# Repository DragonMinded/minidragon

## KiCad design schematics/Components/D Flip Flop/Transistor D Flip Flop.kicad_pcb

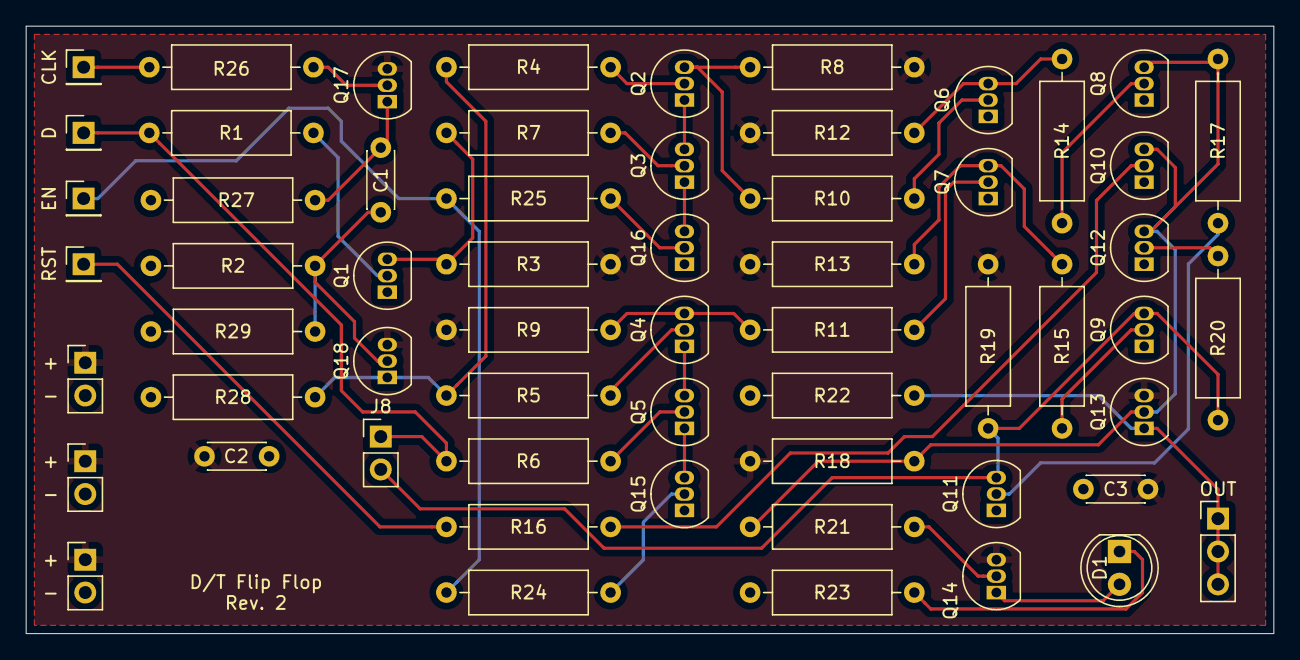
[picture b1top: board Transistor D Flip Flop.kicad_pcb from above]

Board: 2 copper layers, 96.5 x 47.0 mm, 60 parts (0 on the bottom side), 39 nets.

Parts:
C1, C2, C3: 0.1uF; C_Disc_D4.3mm_W1.9mm_P5.00mm
D1: LED; LED_D5.0mm
J1: CLK; PinHeader_1x01_P2.54mm_Vertical
J2: D; PinHeader_1x01_P2.54mm_Vertical
J3: RST; PinHeader_1x01_P2.54mm_Vertical
J4, J5, J6: Power; PinHeader_1x02_P2.54mm_Vertical
J7: OUT; PinHeader_1x03_P2.54mm_Vertical
J8: T-Select; PinHeader_1x02_P2.54mm_Vertical
J9: EN; PinHeader_1x01_P2.54mm_Vertical
Q1, Q2, Q3, Q4, Q5, Q6, Q7, Q8, Q9, Q10, Q11, Q12, Q13, Q14, Q15, Q16, Q17, Q18: 2N2222; TO-92_Inline
R1, R4, R5, R6, R7, R10, R11, R14, R15, R16, R17, R20, R21, R24, R25: 10K; R_Axial_DIN0309_L9.0mm_D3.2mm_P12.70mm_Horizontal
R2, R27, R29: 100; R_Axial_DIN0309_L9.0mm_D3.2mm_P12.70mm_Horizontal
R3, R8, R9, R12, R13, R18, R19, R22, R23, R26, R28: 1K; R_Axial_DIN0309_L9.0mm_D3.2mm_P12.70mm_Horizontal

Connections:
GND: C2.1, C3.1, J4.2, J5.2, J6.2, Q1.1 (E), Q6.1 (E), Q7.1 (E), Q8.1 (E), Q9.1 (E), Q10.1 (E), Q11.1 (E), Q12.1 (E), Q15.1 (E), Q16.1 (E), R2.2, R22.1, R23.1, R27.2, R28.2, R29.2
unnamed: D1.2 (A), Q14.1 (E)
unnamed: D1.1 (K), R23.2
unnamed: J1.1, R26.2
unnamed: J2.1, J8.1, R1.2, R6.2
unnamed: J3.1, R16.2
unnamed: J7.1, J7.2, J7.3, Q13.1 (E), R22.2
unnamed: J8.2, Q9.3 (C), Q11.3 (C), R19.2, R20.2
unnamed: J9.1, R24.2, R25.2
unnamed: Q1.2 (B), R1.1
unnamed: Q1.3 (C), R3.2, R7.2
unnamed: Q2.2 (B), R4.1
unnamed: Q2.3 (C), R8.2, R10.2
unnamed: Q2.1 (E), Q3.3 (C)
unnamed: Q3.2 (B), R7.1
unnamed: Q4.2 (B), R5.1
unnamed: Q4.3 (C), R9.2, R11.2
unnamed: Q4.1 (E), Q5.3 (C)
unnamed: Q5.2 (B), R6.1
unnamed: Q6.2 (B), R10.1
unnamed: Q6.3 (C), R12.2, R14.2
unnamed: Q7.2 (B), R11.1
unnamed: Q7.3 (C), R13.2, R15.2
unnamed: Q8.2 (B), R14.1
unnamed: Q9.2 (B), R15.1
unnamed: Q10.2 (B), R16.1
unnamed: Q8.3 (C), Q10.3 (C), Q12.3 (C), Q13.2 (B), R17.1, R18.1, R21.2
unnamed: Q11.2 (B), R17.2
unnamed: Q12.2 (B), R20.1
unnamed: Q14.2 (B), R21.1
unnamed: Q15.2 (B), R24.1
unnamed: Q5.1 (E), Q15.3 (C)
unnamed: Q16.2 (B), R25.1
unnamed: Q3.1 (E), Q16.3 (C)
unnamed: Q17.2 (B), R26.1
unnamed: C1.1, Q17.1 (E), R27.1
unnamed: C1.2, Q18.2 (B), R2.1, R29.1
unnamed: Q18.1 (E), R4.2, R5.2, R28.1
VCC: C2.2, C3.2, J4.1, J5.1, J6.1, Q13.3 (C), Q14.3 (C), Q17.3 (C), Q18.3 (C), R3.1, R8.1, R9.1, R12.1, R13.1, R18.2, R19.1

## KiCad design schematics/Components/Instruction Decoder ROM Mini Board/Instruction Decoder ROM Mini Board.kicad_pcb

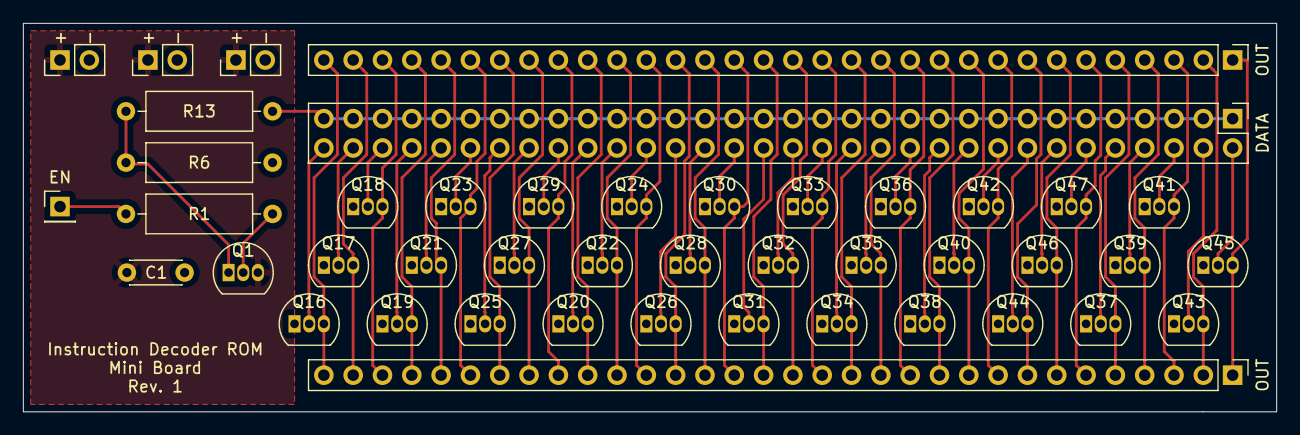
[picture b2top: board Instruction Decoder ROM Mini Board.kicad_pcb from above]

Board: 2 copper layers, 108.6 x 33.7 mm, 44 parts (0 on the bottom side), 70 nets.

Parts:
C1: 0.1uF; C_Disc_D4.3mm_W1.9mm_P5.00mm
J1: EN; PinHeader_1x01_P2.54mm_Vertical
J3, J4, J5: Power; PinHeader_1x02_P2.54mm_Vertical
J7: BIT_4_CONFIG; PinHeader_2x32_P2.54mm_Vertical
J8: MICROCODE_OUTPUT; PinHeader_1x32_P2.54mm_Vertical
J12: MICROCODE_PASSTHROUGH; PinHeader_1x32_P2.54mm_Vertical
Q1, Q16, Q17, Q18, Q19, Q20, Q21, Q22, Q23, Q24, Q25, Q26, Q27, Q28, Q29, Q30, Q31, Q32, Q33, Q34, Q35, Q36, Q37, Q38, Q39, Q40, Q41, Q42, Q43, Q44, Q45, Q46, Q47: 2N2222; TO-92_Inline
R1: 10K; R_Axial_DIN0309_L9.0mm_D3.2mm_P12.70mm_Horizontal
R6, R13: 1K; R_Axial_DIN0309_L9.0mm_D3.2mm_P12.70mm_Horizontal

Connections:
GND: C1.2, J3.2, J4.2, J5.2, Q16.1 (E), Q17.1 (E), Q18.1 (E), Q19.1 (E), Q20.1 (E), Q21.1 (E), Q22.1 (E), Q23.1 (E), Q24.1 (E), Q25.1 (E), Q26.1 (E), Q27.1 (E), Q28.1 (E), Q29.1 (E), Q30.1 (E), Q31.1 (E), Q32.1 (E), Q33.1 (E), Q34.1 (E), Q35.1 (E), Q36.1 (E), Q37.1 (E), Q38.1 (E), Q39.1 (E), Q40.1 (E), Q41.1 (E), Q42.1 (E), Q43.1 (E), Q44.1 (E), Q45.1 (E), Q46.1 (E), Q47.1 (E), R6.2
unnamed: J1.1, R1.2
unnamed: J7.1, J7.3, J7.5, J7.7, J7.9, J7.11, J7.13, J7.15, J7.17, J7.19, J7.21, J7.23, J7.25, J7.27, J7.29, J7.31, J7.33, J7.35, J7.37, J7.39, J7.41, J7.43, J7.45, J7.47, J7.49, J7.51, J7.53, J7.55, J7.57, J7.59, J7.61, J7.63, R13.1
unnamed: J7.2, Q45.2 (B)
unnamed: J7.4, Q43.2 (B)
unnamed: J7.6, Q41.2 (B)
unnamed: J7.8, Q39.2 (B)
unnamed: J7.10, Q37.2 (B)
unnamed: J7.12, Q47.2 (B)
unnamed: J7.14, Q46.2 (B)
unnamed: J7.16, Q44.2 (B)
unnamed: J7.18, Q42.2 (B)
unnamed: J7.20, Q40.2 (B)
unnamed: J7.22, Q38.2 (B)
unnamed: J7.24, Q36.2 (B)
unnamed: J7.26, Q35.2 (B)
unnamed: J7.28, Q34.2 (B)
unnamed: J7.30, Q33.2 (B)
unnamed: J7.32, Q32.2 (B)
unnamed: J7.34, Q31.2 (B)
unnamed: J7.36, Q30.2 (B)
unnamed: J7.38, Q28.2 (B)
unnamed: J7.40, Q26.2 (B)
unnamed: J7.42, Q24.2 (B)
unnamed: J7.44, Q22.2 (B)
unnamed: J7.46, Q20.2 (B)
unnamed: J7.48, Q29.2 (B)
unnamed: J7.50, Q27.2 (B)
unnamed: J7.52, Q25.2 (B)
unnamed: J7.54, Q23.2 (B)
unnamed: J7.56, Q21.2 (B)
unnamed: J7.58, Q19.2 (B)
unnamed: J7.60, Q18.2 (B)
unnamed: J7.62, Q17.2 (B)
unnamed: J7.64, Q16.2 (B)
unnamed: J8.1, J12.1, Q45.3 (C)
unnamed: J8.2, J12.2, Q43.3 (C)
unnamed: J8.3, J12.3, Q41.3 (C)
unnamed: J8.4, J12.4, Q39.3 (C)
unnamed: J8.5, J12.5, Q37.3 (C)
unnamed: J8.6, J12.6, Q47.3 (C)
unnamed: J8.7, J12.7, Q46.3 (C)
unnamed: J8.8, J12.8, Q44.3 (C)
unnamed: J8.9, J12.9, Q42.3 (C)
unnamed: J8.10, J12.10, Q40.3 (C)
unnamed: J8.11, J12.11, Q38.3 (C)
unnamed: J8.12, J12.12, Q36.3 (C)
unnamed: J8.13, J12.13, Q35.3 (C)
unnamed: J8.14, J12.14, Q34.3 (C)
unnamed: J8.15, J12.15, Q33.3 (C)
unnamed: J8.16, J12.16, Q32.3 (C)
unnamed: J8.17, J12.17, Q31.3 (C)
unnamed: J8.18, J12.18, Q30.3 (C)
unnamed: J8.19, J12.19, Q28.3 (C)
unnamed: J8.20, J12.20, Q26.3 (C)
unnamed: J8.21, J12.21, Q24.3 (C)
unnamed: J8.22, J12.22, Q22.3 (C)
unnamed: J8.23, J12.23, Q20.3 (C)
unnamed: J8.24, J12.24, Q29.3 (C)
unnamed: J8.25, J12.25, Q27.3 (C)
unnamed: J8.26, J12.26, Q25.3 (C)
unnamed: J8.27, J12.27, Q23.3 (C)
unnamed: J8.28, J12.28, Q21.3 (C)
unnamed: J8.29, J12.29, Q19.3 (C)
unnamed: J8.30, J12.30, Q18.3 (C)
unnamed: J8.31, J12.31, Q17.3 (C)
unnamed: J8.32, J12.32, Q16.3 (C)
unnamed: Q1.2 (B), R1.1
unnamed: Q1.1 (E), R6.1, R13.2
VCC: C1.1, J3.1, J4.1, J5.1, Q1.3 (C)

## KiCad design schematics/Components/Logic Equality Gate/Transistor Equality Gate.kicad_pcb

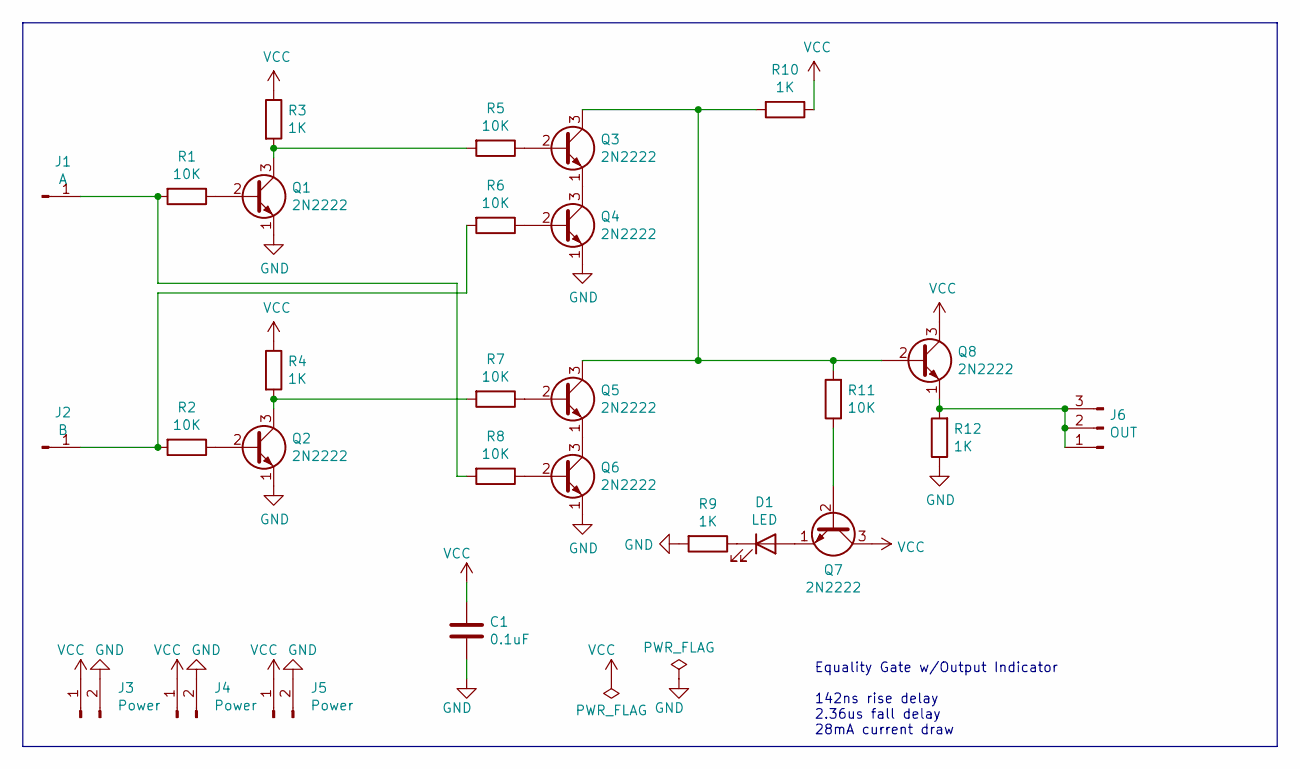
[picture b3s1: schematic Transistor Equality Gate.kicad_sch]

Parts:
C1: 0.1uF; C_Disc_D4.3mm_W1.9mm_P5.00mm
D1: LED; LED_D5.0mm
J1: A; PinHeader_1x01_P2.54mm_Vertical
J2: B; PinHeader_1x01_P2.54mm_Vertical
J3, J4, J5: Power; PinHeader_1x02_P2.54mm_Vertical
J6: OUT; PinHeader_1x03_P2.54mm_Vertical
Q1, Q2, Q3, Q4, Q5, Q6, Q7, Q8: 2N2222; TO-92_Inline
R1, R2, R5, R6, R7, R8, R11: 10K; R_Axial_DIN0309_L9.0mm_D3.2mm_P12.70mm_Horizontal
R3, R4, R9, R10, R12: 1K; R_Axial_DIN0309_L9.0mm_D3.2mm_P12.70mm_Horizontal

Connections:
GND: C1.2, J3.2, J4.2, J5.2, Q1.1 (E), Q2.1 (E), Q4.1 (E), Q6.1 (E), R9.2, R12.1
unnamed: D1.2 (A), Q7.1 (E)
unnamed: D1.1 (K), R9.1
unnamed: J1.1, R1.2, R8.2
unnamed: J2.1, R2.2, R6.2
unnamed: J6.1, J6.2, J6.3, Q8.1 (E), R12.2
unnamed: Q1.2 (B), R1.1
unnamed: Q1.3 (C), R3.2, R5.2
unnamed: Q2.2 (B), R2.1
unnamed: Q2.3 (C), R4.2, R7.2
unnamed: Q3.2 (B), R5.1
unnamed: Q3.3 (C), Q5.3 (C), Q8.2 (B), R10.2, R11.2
unnamed: Q3.1 (E), Q4.3 (C)
unnamed: Q4.2 (B), R6.1
unnamed: Q5.2 (B), R7.1
unnamed: Q5.1 (E), Q6.3 (C)
unnamed: Q6.2 (B), R8.1
unnamed: Q7.2 (B), R11.1
VCC: C1.1, J3.1, J4.1, J5.1, Q7.3 (C), Q8.3 (C), R3.1, R4.1, R10.1

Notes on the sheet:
Equality Gate w/Output Indicator 142ns rise delay 2.36us fall delay 28mA current draw

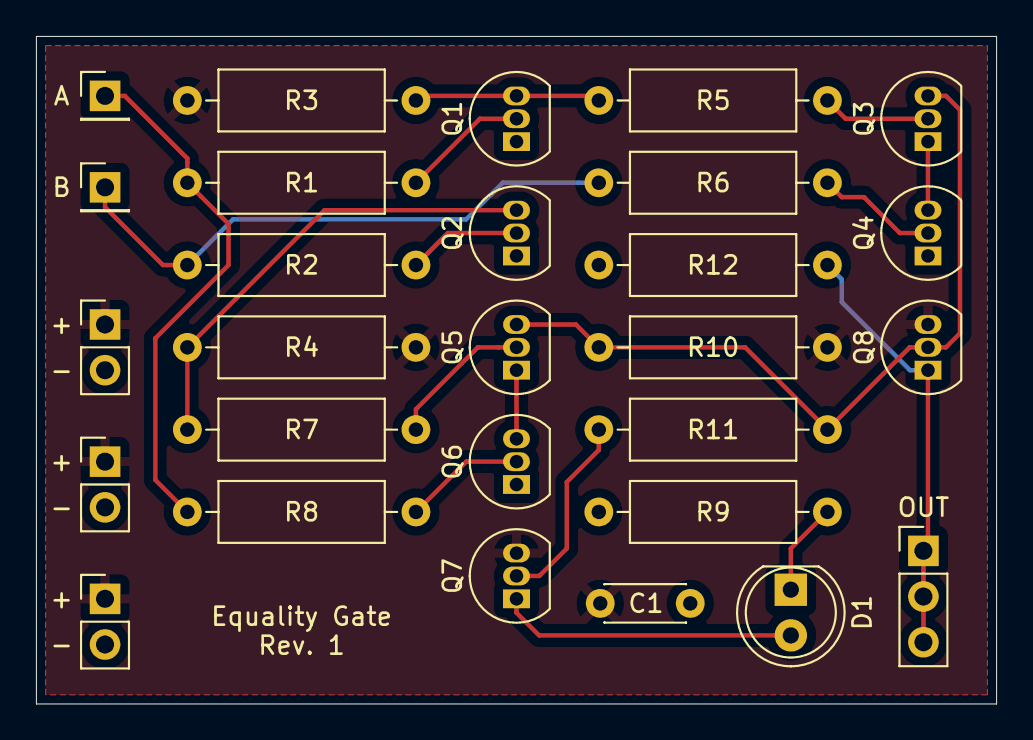
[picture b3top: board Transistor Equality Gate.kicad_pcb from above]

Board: 2 copper layers, 53.3 x 37.1 mm, 28 parts (0 on the bottom side), 19 nets.

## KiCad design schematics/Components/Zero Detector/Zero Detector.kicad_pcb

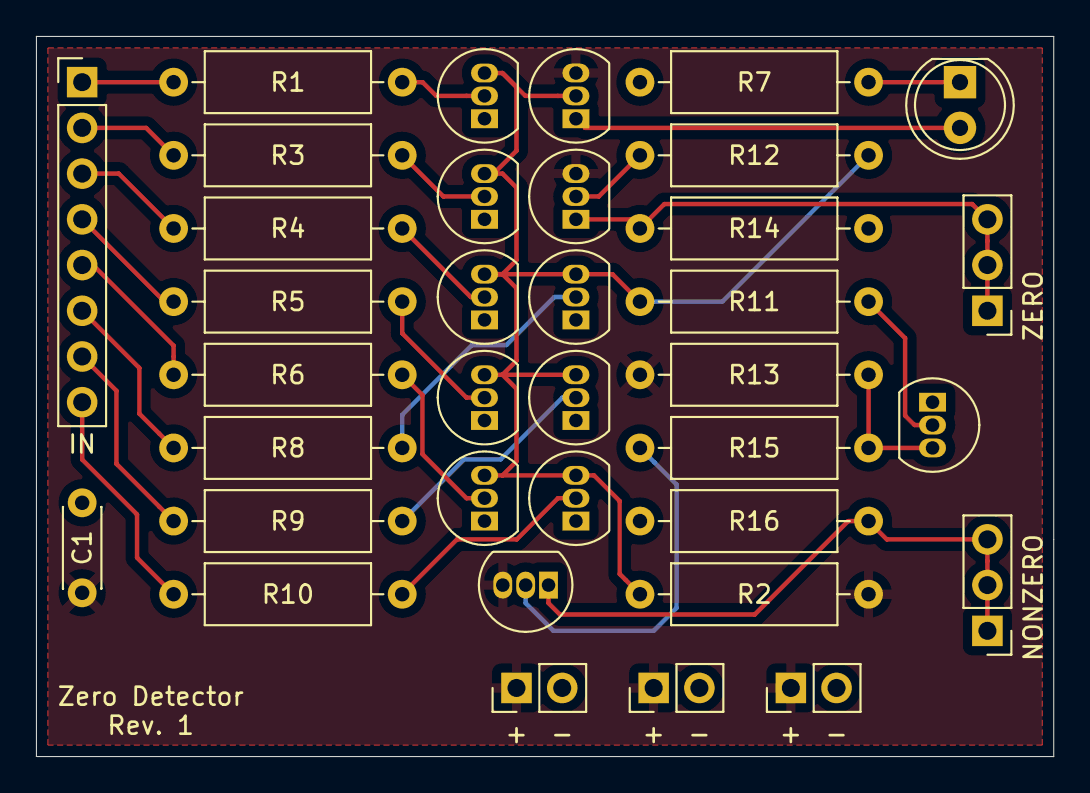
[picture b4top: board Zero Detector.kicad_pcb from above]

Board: 2 copper layers, 56.5 x 40.0 mm, 36 parts (0 on the bottom side), 27 nets.

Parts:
C1: 0.1uF; C_Disc_D4.3mm_W1.9mm_P5.00mm
D1: LED; LED_D5.0mm
J1, J3, J4: POWER; PinHeader_1x02_P2.54mm_Vertical
J2: IN; PinHeader_1x08_P2.54mm_Vertical
J5: ZERO; PinHeader_1x03_P2.54mm_Vertical
J6: NONZERO; PinHeader_1x03_P2.54mm_Vertical
Q1, Q2, Q3, Q4, Q5, Q6, Q7, Q8, Q9, Q10, Q11, Q12: 2N2222; TO-92_Inline
R1, R3, R4, R5, R6, R8, R9, R10, R11, R12, R15: 10K; R_Axial_DIN0309_L9.0mm_D3.2mm_P12.70mm_Horizontal
R2, R7, R13, R14, R16: 1K; R_Axial_DIN0309_L9.0mm_D3.2mm_P12.70mm_Horizontal

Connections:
GND: C1.2, J1.2, J3.2, J4.2, Q1.1 (E), Q2.1 (E), Q3.1 (E), Q4.1 (E), Q6.1 (E), Q7.1 (E), Q8.1 (E), Q9.1 (E), Q10.1 (E), R7.2, R14.2, R16.2
unnamed: D1.2 (A), Q5.1 (E)
unnamed: D1.1 (K), R7.1
unnamed: J2.1, R1.2
unnamed: J2.2, R3.2
unnamed: J2.3, R4.2
unnamed: J2.4, R5.2
unnamed: J2.5, R6.2
unnamed: J2.6, R8.2
unnamed: J2.7, R9.2
unnamed: J2.8, R10.2
unnamed: J5.1, J5.2, J5.3, Q11.1 (E), R14.1
unnamed: J6.1, J6.2, J6.3, Q12.1 (E), R16.1
unnamed: Q1.2 (B), R3.1
unnamed: Q1.3 (C), Q2.3 (C), Q3.3 (C), Q4.3 (C), Q5.2 (B), Q6.3 (C), Q7.3 (C), Q8.3 (C), Q9.3 (C), R2.1, R11.2, R12.2
unnamed: Q2.2 (B), R1.1
unnamed: Q3.2 (B), R4.1
unnamed: Q4.2 (B), R5.1
unnamed: Q6.2 (B), R6.1
unnamed: Q7.2 (B), R8.1
unnamed: Q8.2 (B), R9.1
unnamed: Q9.2 (B), R10.1
unnamed: Q10.2 (B), R11.1
unnamed: Q10.3 (C), R13.2, R15.2
unnamed: Q11.2 (B), R12.1
unnamed: Q12.2 (B), R15.1
VCC: C1.1, J1.1, J3.1, J4.1, Q5.3 (C), Q11.3 (C), Q12.3 (C), R2.2, R13.1

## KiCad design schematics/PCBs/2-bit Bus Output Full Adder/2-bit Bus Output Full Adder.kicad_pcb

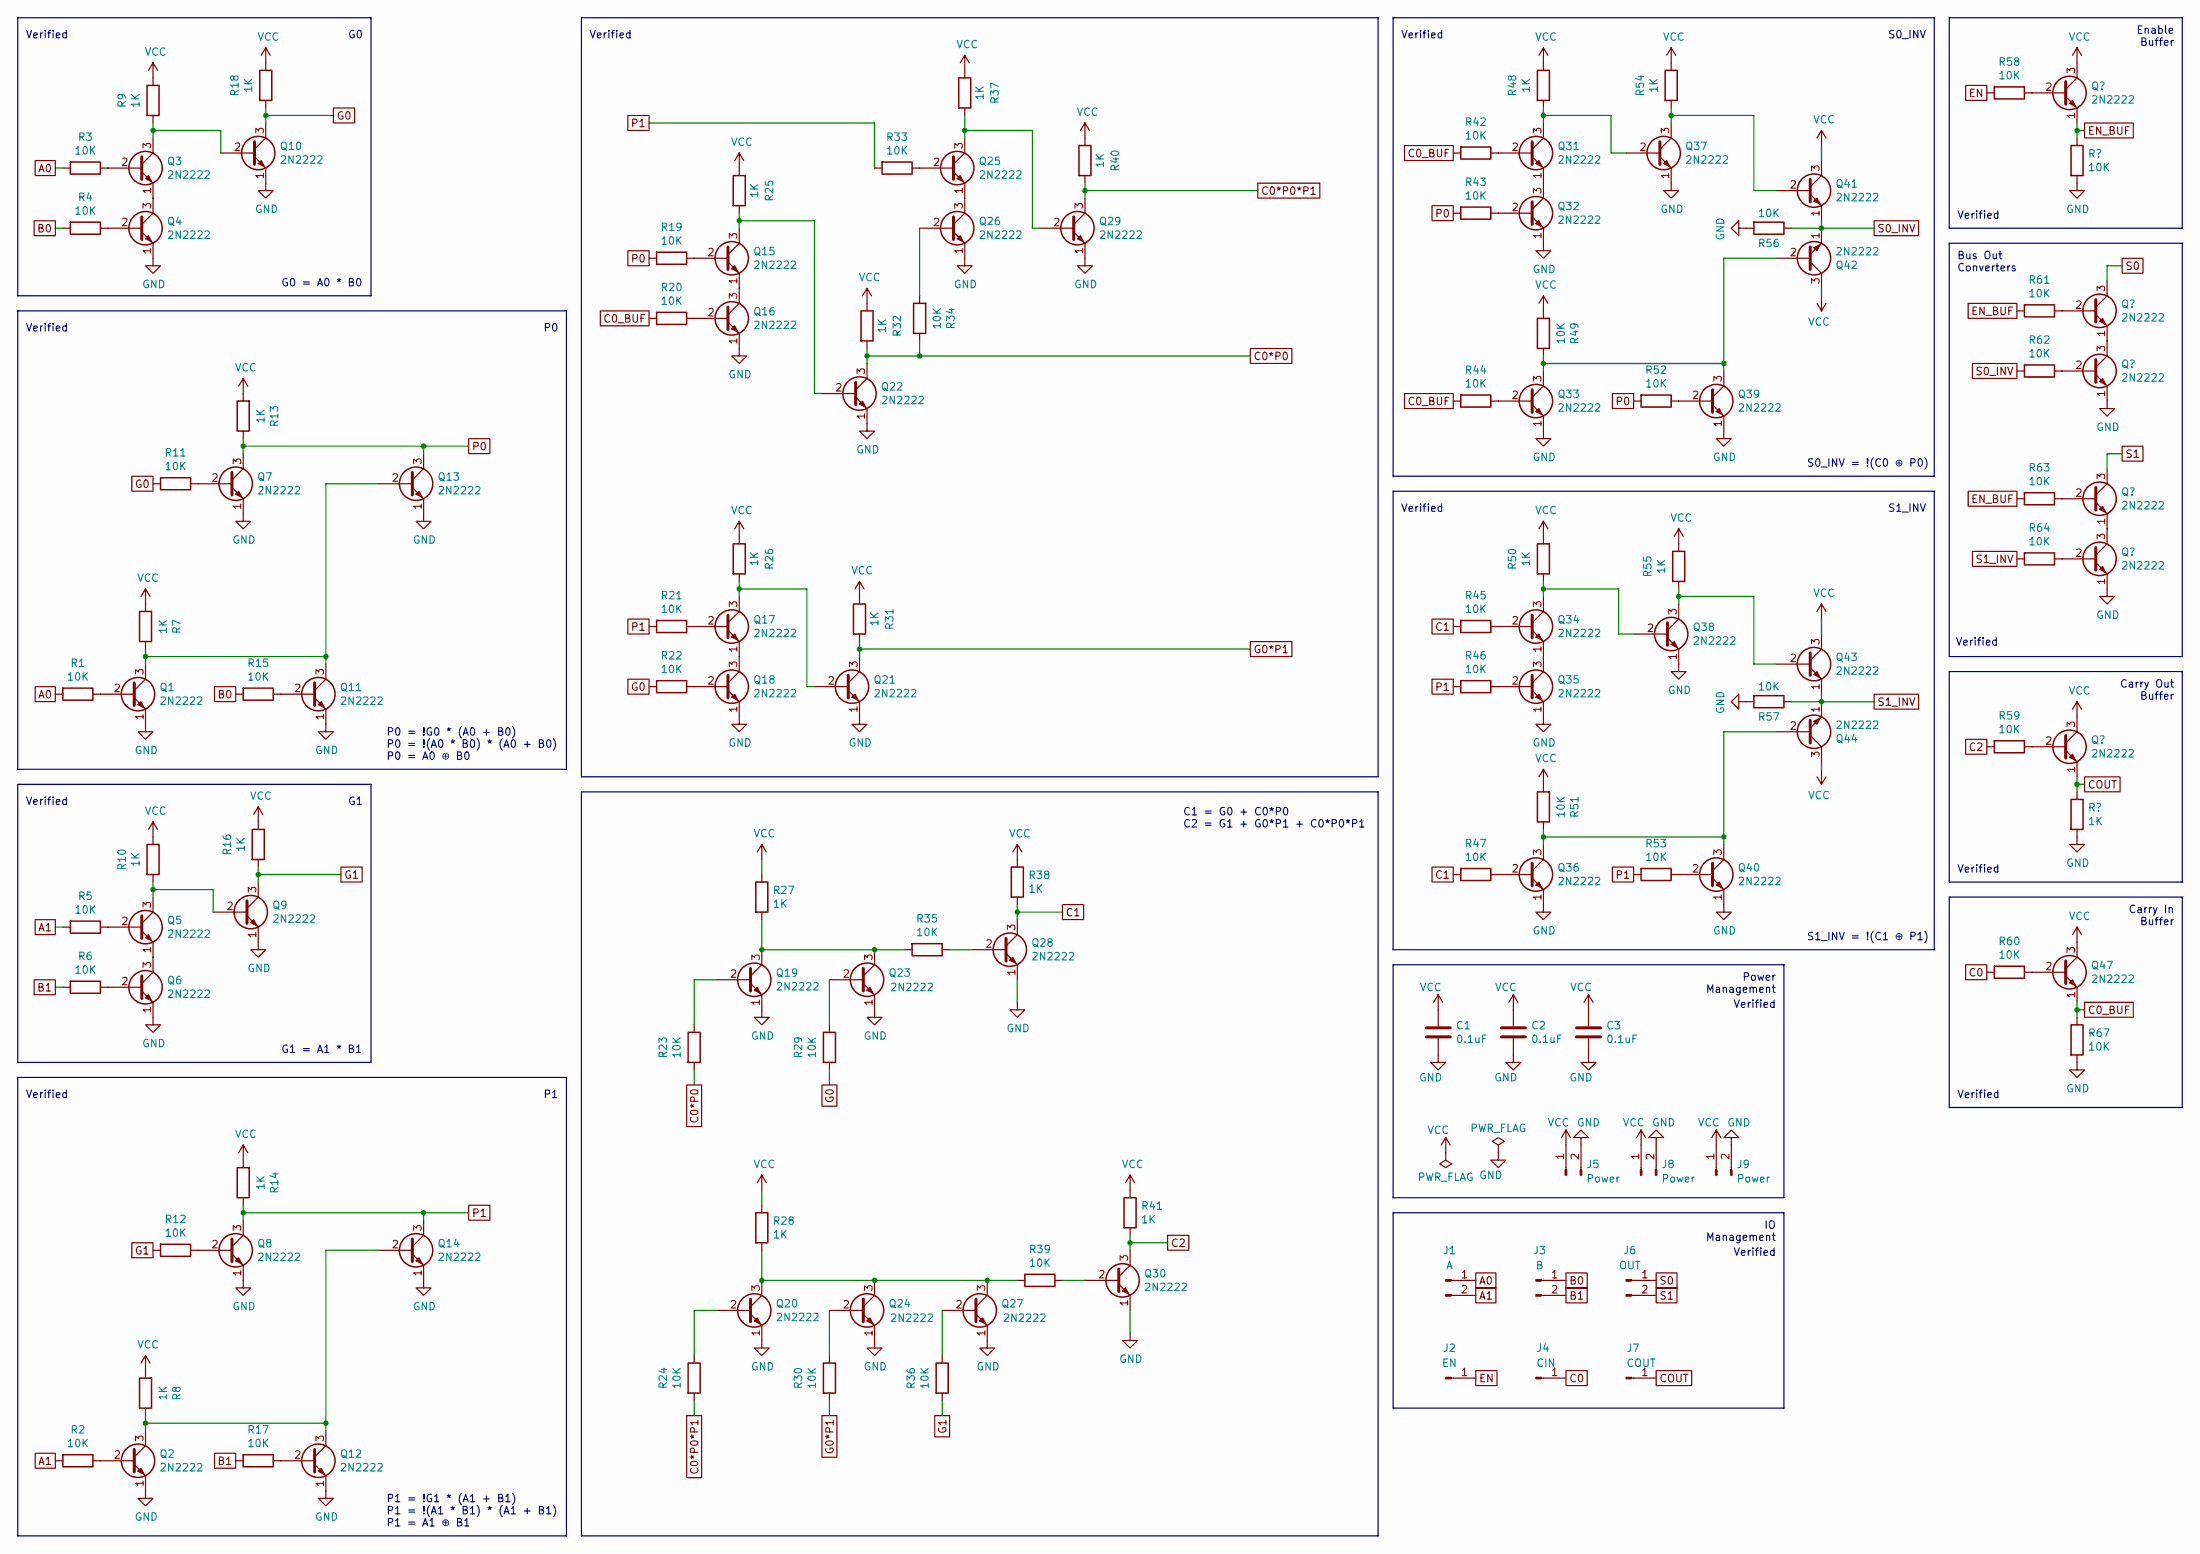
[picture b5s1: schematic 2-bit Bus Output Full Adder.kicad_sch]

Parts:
C1, C2, C3: 0.1uF; C_Disc_D4.3mm_W1.9mm_P5.00mm
J1: A; PinHeader_1x02_P2.54mm_Vertical
J2: EN; PinHeader_1x01_P2.54mm_Vertical
J3: B; PinHeader_1x02_P2.54mm_Vertical
J4: CIN; PinHeader_1x01_P2.54mm_Vertical
J5, J8, J9: Power; PinHeader_1x02_P2.54mm_Vertical
J6: OUT; PinHeader_1x02_P2.54mm_Vertical
J7: COUT; PinHeader_1x01_P2.54mm_Vertical
Q1, Q2, Q3, Q4, Q5, Q6, Q7, Q8, Q9, Q10, Q11, Q12, Q13, Q14, Q15, Q16, Q17, Q18, Q19, Q20, Q21, Q22, Q23, Q24, Q25, Q26, Q27, Q28, Q29, Q30, Q31, Q32, Q33, Q34, Q35, Q36, Q37, Q38, Q39, Q40, Q41, Q42, Q43, Q44, Q45, Q46, Q47, Q48, Q49, Q50, Q51: 2N2222; TO-92_Inline
R1, R2, R3, R4, R5, R6, R11, R12, R15, R17, R19, R20, R21, R22, R23, R24, R29, R30, R33, R34, R35, R36, R39, R42, R43, R44, R45, R46, R47, R49, R51, R52, R53, R56, R57, R58, R59, R60, R61, R62, R63, R64, R65, R67: 10K; R_Axial_DIN0309_L9.0mm_D3.2mm_P12.70mm_Horizontal
R7, R8, R9, R10, R13, R14, R16, R18, R25, R26, R27, R28, R31, R32, R37, R38, R40, R41, R48, R50, R54, R55, R66: 1K; R_Axial_DIN0309_L9.0mm_D3.2mm_P12.70mm_Horizontal

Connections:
A0: J1.1, R1.2, R3.2
A1: J1.2, R2.2, R5.2
B0: J3.1, R4.2, R15.2
B1: J3.2, R6.2, R17.2
C0: J4.1, R60.2
C0*P0: Q22.3 (C), R23.2, R32.2, R34.1
C0*P0*P1: Q29.3 (C), R24.2, R40.2
C0_BUF: Q47.1 (E), R20.2, R42.2, R44.2, R67.1
C1: Q28.3 (C), R38.2, R45.2, R47.2
C2: Q30.3 (C), R41.2, R59.2
COUT: J7.1, Q46.1 (E), R66.1
EN: J2.1, R58.2
EN_BUF: Q45.1 (E), R61.2, R63.2, R65.1
G0: Q10.3 (C), R11.2, R18.2, R22.2, R29.2
G0*P1: Q21.3 (C), R30.2, R31.2
G1: Q9.3 (C), R12.2, R16.2, R36.2
GND: C1.2, C2.2, C3.2, J5.2, J8.2, J9.2, Q1.1 (E), Q2.1 (E), Q4.1 (E), Q6.1 (E), Q7.1 (E), Q8.1 (E), Q9.1 (E), Q10.1 (E), Q11.1 (E), Q12.1 (E), Q13.1 (E), Q14.1 (E), Q16.1 (E), Q18.1 (E), Q19.1 (E), Q20.1 (E), Q21.1 (E), Q22.1 (E), Q23.1 (E), Q24.1 (E), Q26.1 (E), Q27.1 (E), Q28.1 (E), Q29.1 (E), Q30.1 (E), Q32.1 (E), Q33.1 (E), Q35.1 (E), Q36.1 (E), Q37.1 (E), Q38.1 (E), Q39.1 (E), Q40.1 (E), Q49.1 (E), Q51.1 (E), R56.2, R57.2, R65.2, R66.2, R67.2
unnamed: Q1.2 (B), R1.1
unnamed: Q1.3 (C), Q11.3 (C), Q13.2 (B), R7.1
unnamed: Q2.2 (B), R2.1
unnamed: Q3.2 (B), R3.1
unnamed: Q3.1 (E), Q4.3 (C)
unnamed: Q4.2 (B), R4.1
unnamed: Q5.2 (B), R5.1
unnamed: Q5.3 (C), Q9.2 (B), R10.2
unnamed: Q5.1 (E), Q6.3 (C)
unnamed: Q6.2 (B), R6.1
unnamed: Q7.2 (B), R11.1
unnamed: Q8.2 (B), R12.1
unnamed: Q3.3 (C), Q10.2 (B), R9.2
unnamed: Q11.2 (B), R15.1
unnamed: Q12.2 (B), R17.1
unnamed: Q2.3 (C), Q12.3 (C), Q14.2 (B), R8.1
unnamed: Q15.2 (B), R19.1
unnamed: Q15.3 (C), Q22.2 (B), R25.2
unnamed: Q15.1 (E), Q16.3 (C)
unnamed: Q16.2 (B), R20.1
unnamed: Q17.2 (B), R21.1
unnamed: Q17.3 (C), Q21.2 (B), R26.2
unnamed: Q17.1 (E), Q18.3 (C)
unnamed: Q18.2 (B), R22.1
unnamed: Q19.2 (B), R23.1
unnamed: Q19.3 (C), Q23.3 (C), R27.2, R35.2
unnamed: Q20.2 (B), R24.1
unnamed: Q20.3 (C), Q24.3 (C), Q27.3 (C), R28.2, R39.2
unnamed: Q23.2 (B), R29.1
unnamed: Q24.2 (B), R30.1
unnamed: Q25.2 (B), R33.1
unnamed: Q25.3 (C), Q29.2 (B), R37.2
unnamed: Q25.1 (E), Q26.3 (C)
unnamed: Q26.2 (B), R34.2
unnamed: Q27.2 (B), R36.1
unnamed: Q28.2 (B), R35.1
unnamed: Q30.2 (B), R39.1
unnamed: Q31.2 (B), R42.1
unnamed: Q31.3 (C), Q37.2 (B), R48.2
unnamed: Q31.1 (E), Q32.3 (C)
unnamed: Q32.2 (B), R43.1
unnamed: Q33.2 (B), R44.1
unnamed: Q33.3 (C), Q39.3 (C), Q42.2 (B), R49.1
unnamed: Q34.2 (B), R45.1
unnamed: Q34.3 (C), Q38.2 (B), R50.2
unnamed: Q34.1 (E), Q35.3 (C)
unnamed: Q35.2 (B), R46.1
unnamed: Q36.2 (B), R47.1
unnamed: Q36.3 (C), Q40.3 (C), Q44.2 (B), R51.1
unnamed: Q37.3 (C), Q41.2 (B), R54.2
unnamed: Q38.3 (C), Q43.2 (B), R55.2
unnamed: Q39.2 (B), R52.1
unnamed: Q40.2 (B), R53.1
unnamed: Q45.2 (B), R58.1
unnamed: Q46.2 (B), R59.1
unnamed: Q47.2 (B), R60.1
unnamed: Q48.2 (B), R61.1
unnamed: Q48.1 (E), Q49.3 (C)
unnamed: Q49.2 (B), R62.1
unnamed: Q50.2 (B), R63.1
unnamed: Q50.1 (E), Q51.3 (C)
unnamed: Q51.2 (B), R64.1
P0: Q7.3 (C), Q13.3 (C), R13.1, R19.2, R43.2, R52.2
P1: Q8.3 (C), Q14.3 (C), R14.1, R21.2, R33.2, R46.2, R53.2
S0: J6.1, Q48.3 (C)
S0_INV: Q41.1 (E), Q42.1 (E), R56.1, R62.2
S1: J6.2, Q50.3 (C)
S1_INV: Q43.1 (E), Q44.1 (E), R57.1, R64.2
VCC: C1.1, C2.1, C3.1, J5.1, J8.1, J9.1, Q41.3 (C), Q42.3 (C), Q43.3 (C), Q44.3 (C), Q45.3 (C), Q46.3 (C), Q47.3 (C), R7.2, R8.2, R9.1, R10.1, R13.2, R14.2, R16.1, R18.1, R25.1, R26.1, R27.1, R28.1, R31.1, R32.1, R37.1, R38.1, R40.1, R41.1, R48.1, R49.2, R50.1, R51.2, R54.1, R55.1

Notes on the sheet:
Verified
S0_INV = !(C0 ⊕ P0)
Carry In Buffer
S0_INV
S1_INV
Carry Out Buffer
G1 = A1 * B1
S1_INV = !(C1 ⊕ P1)
C1 = G0 + C0*P0 C2 = G1 + G0*P1 + C0*P0*P1
Power Management
Enable Buffer
IO Management
G0 = A0 * B0
P1 = !G1 * (A1 + B1) P1 = !(A1 * B1) * (A1 + B1) P1 = A1 ⊕ B1
P0 = !G0 * (A0 + B0) P0 = !(A0 * B0) * (A0 + B0) P0 = A0 ⊕ B0
Bus Out Converters

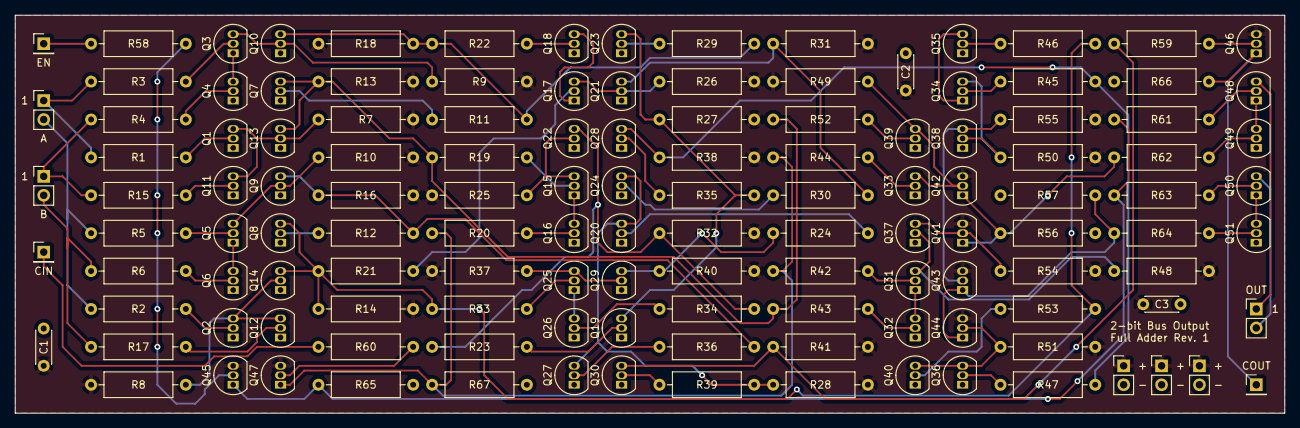
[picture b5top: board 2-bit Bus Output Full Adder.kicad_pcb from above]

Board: 2 copper layers, 170.2 x 53.3 mm, 130 parts (0 on the bottom side), 86 nets.

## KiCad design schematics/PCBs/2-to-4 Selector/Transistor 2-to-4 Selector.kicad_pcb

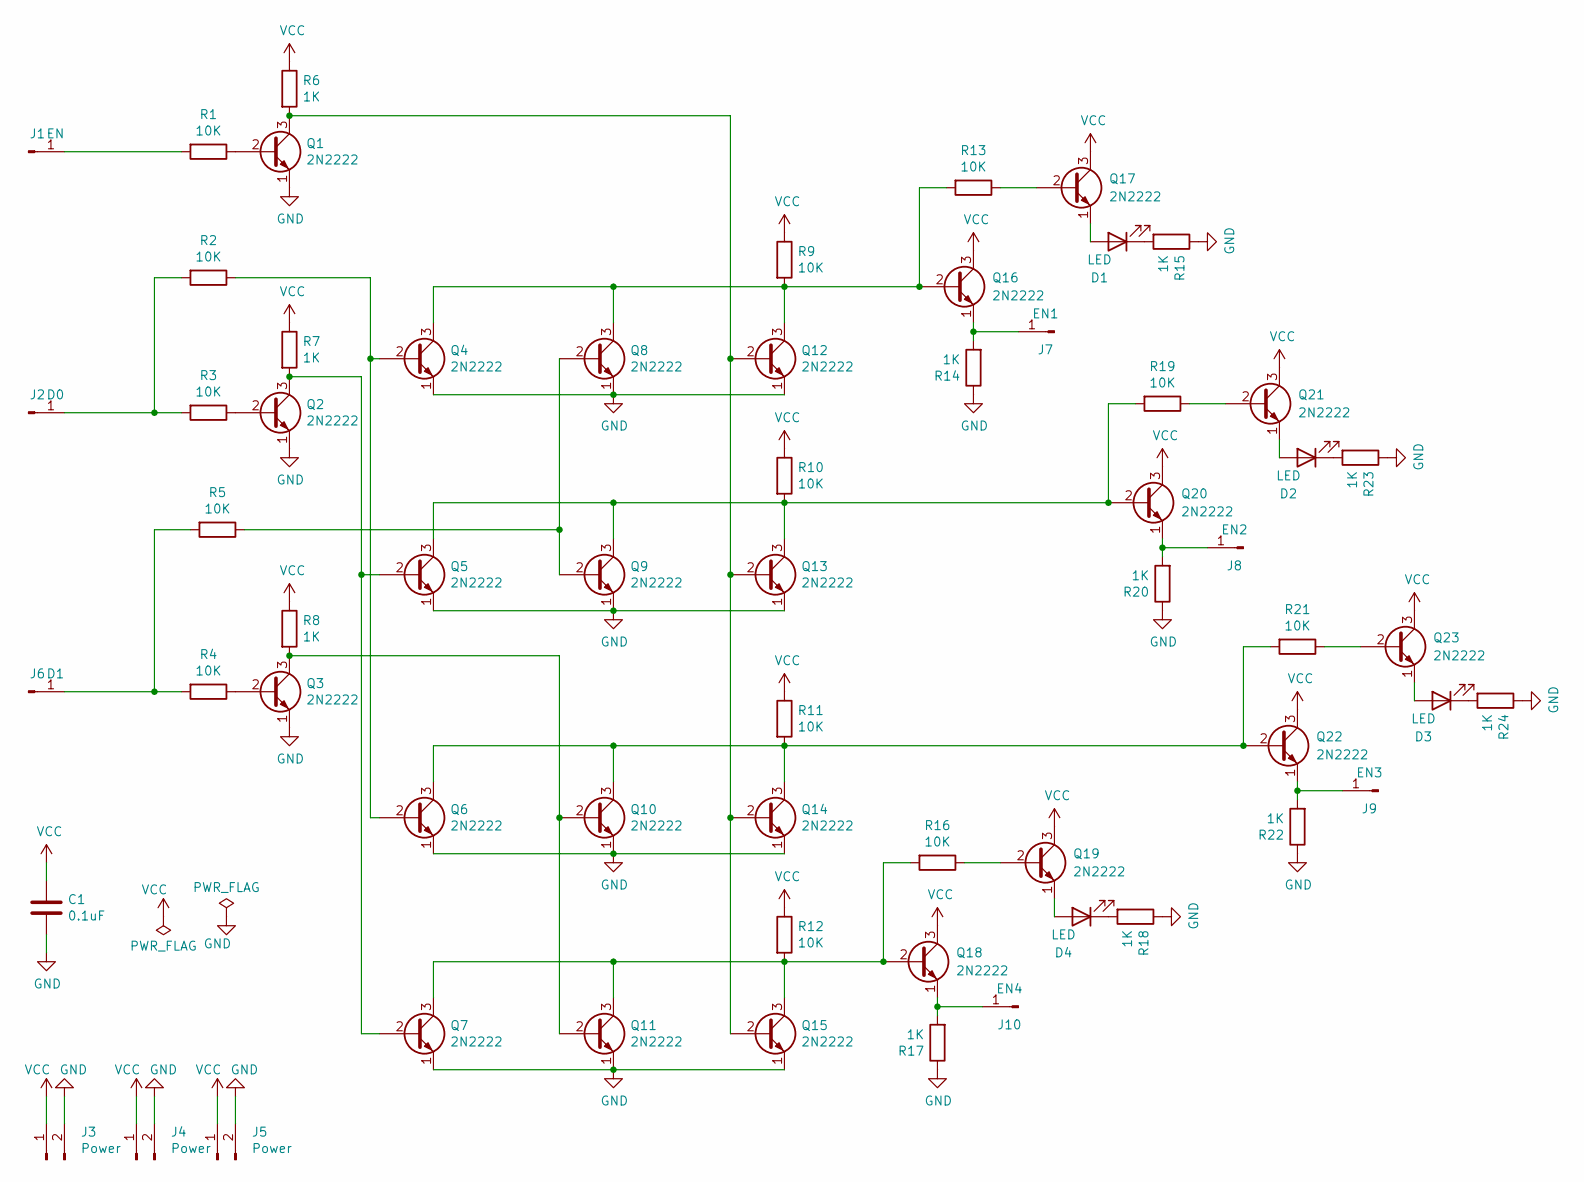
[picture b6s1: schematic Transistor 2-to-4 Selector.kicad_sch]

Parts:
C1: 0.1uF; C_Disc_D4.3mm_W1.9mm_P5.00mm
D1, D2, D3, D4: LED; LED_D5.0mm
J1: EN; PinHeader_1x01_P2.54mm_Vertical
J2: D0; PinHeader_1x01_P2.54mm_Vertical
J3, J4, J5: Power; PinHeader_1x02_P2.54mm_Vertical
J6: D1; PinHeader_1x01_P2.54mm_Vertical
J7: EN1; PinHeader_1x01_P2.54mm_Vertical
J8: EN2; PinHeader_1x01_P2.54mm_Vertical
J9: EN3; PinHeader_1x01_P2.54mm_Vertical
J10: EN4; PinHeader_1x01_P2.54mm_Vertical
Q1, Q2, Q3, Q4, Q5, Q6, Q7, Q8, Q9, Q10, Q11, Q12, Q13, Q14, Q15, Q16, Q17, Q18, Q19, Q20, Q21, Q22, Q23: 2N2222; TO-92_Inline
R1, R2, R3, R4, R5, R9, R10, R11, R12, R13, R16, R19, R21: 10K; R_Axial_DIN0309_L9.0mm_D3.2mm_P12.70mm_Horizontal
R6, R7, R8, R14, R15, R17, R18, R20, R22, R23, R24: 1K; R_Axial_DIN0309_L9.0mm_D3.2mm_P12.70mm_Horizontal

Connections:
GND: C1.2, J3.2, J4.2, J5.2, Q1.1 (E), Q2.1 (E), Q3.1 (E), Q4.1 (E), Q5.1 (E), Q6.1 (E), Q7.1 (E), Q8.1 (E), Q9.1 (E), Q10.1 (E), Q11.1 (E), Q12.1 (E), Q13.1 (E), Q14.1 (E), Q15.1 (E), R14.1, R15.1, R17.1, R18.1, R20.1, R22.1, R23.1, R24.1
unnamed: D1.2 (A), Q17.1 (E)
unnamed: D1.1 (K), R15.2
unnamed: D2.2 (A), Q21.1 (E)
unnamed: D2.1 (K), R23.2
unnamed: D3.2 (A), Q23.1 (E)
unnamed: D3.1 (K), R24.2
unnamed: D4.2 (A), Q19.1 (E)
unnamed: D4.1 (K), R18.2
unnamed: J1.1, R1.2
unnamed: J2.1, R2.2, R3.2
unnamed: J6.1, R4.2, R5.2
unnamed: J7.1, Q16.1 (E), R14.2
unnamed: J8.1, Q20.1 (E), R20.2
unnamed: J9.1, Q22.1 (E), R22.2
unnamed: J10.1, Q18.1 (E), R17.2
unnamed: Q1.2 (B), R1.1
unnamed: Q1.3 (C), Q12.2 (B), Q13.2 (B), Q14.2 (B), Q15.2 (B), R6.2
unnamed: Q2.2 (B), R3.1
unnamed: Q2.3 (C), Q5.2 (B), Q7.2 (B), R7.2
unnamed: Q3.2 (B), R4.1
unnamed: Q4.2 (B), Q6.2 (B), R2.1
unnamed: Q8.2 (B), Q9.2 (B), R5.1
unnamed: Q3.3 (C), Q10.2 (B), Q11.2 (B), R8.2
unnamed: Q6.3 (C), Q10.3 (C), Q14.3 (C), Q22.2 (B), R11.2, R21.2
unnamed: Q7.3 (C), Q11.3 (C), Q15.3 (C), Q18.2 (B), R12.2, R16.2
unnamed: Q4.3 (C), Q8.3 (C), Q12.3 (C), Q16.2 (B), R9.2, R13.2
unnamed: Q5.3 (C), Q9.3 (C), Q13.3 (C), Q20.2 (B), R10.2, R19.2
unnamed: Q17.2 (B), R13.1
unnamed: Q19.2 (B), R16.1
unnamed: Q21.2 (B), R19.1
unnamed: Q23.2 (B), R21.1
VCC: C1.1, J3.1, J4.1, J5.1, Q16.3 (C), Q17.3 (C), Q18.3 (C), Q19.3 (C), Q20.3 (C), Q21.3 (C), Q22.3 (C), Q23.3 (C), R6.1, R7.1, R8.1, R9.1, R10.1, R11.1, R12.1

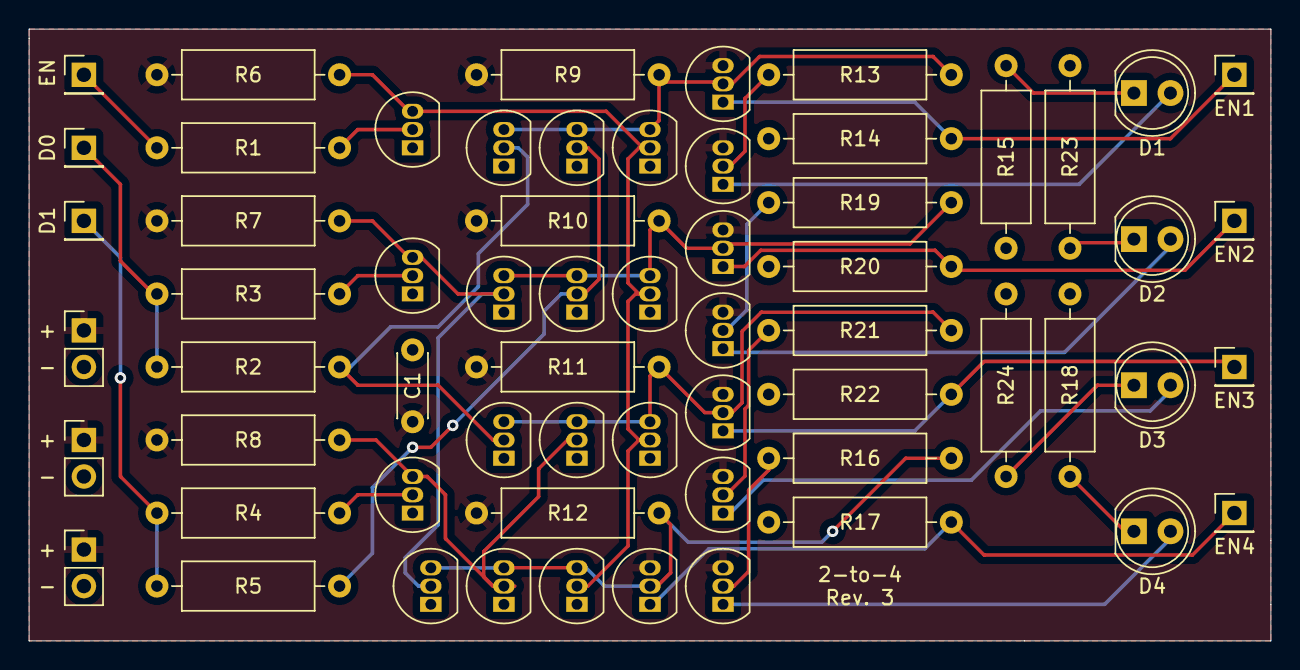
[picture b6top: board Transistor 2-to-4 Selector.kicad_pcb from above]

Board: 2 copper layers, 86.4 x 42.5 mm, 62 parts (0 on the bottom side), 33 nets.

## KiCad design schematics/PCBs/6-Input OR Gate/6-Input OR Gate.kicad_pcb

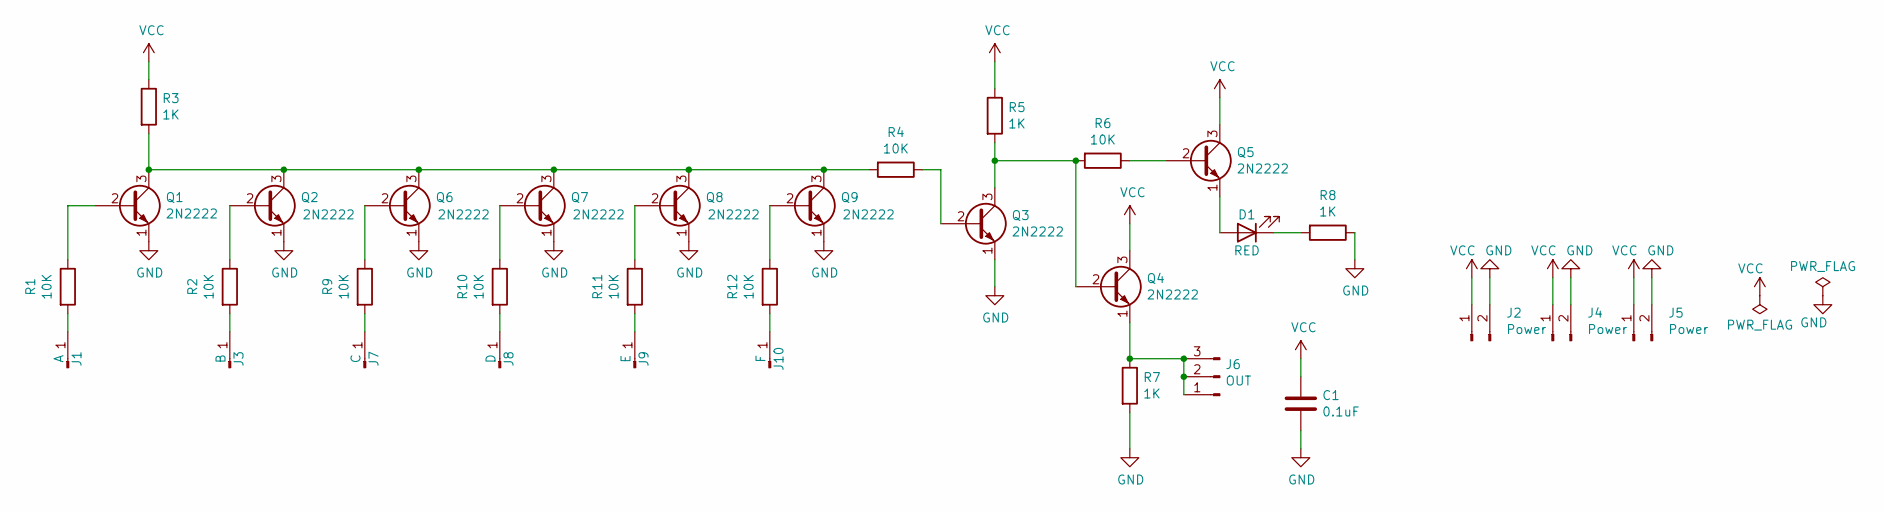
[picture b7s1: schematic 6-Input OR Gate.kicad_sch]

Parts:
C1: 0.1uF; C_Disc_D4.3mm_W1.9mm_P5.00mm
D1: RED; LED_D5.0mm
J1: A; PinHeader_1x01_P2.54mm_Vertical
J2, J4, J5: Power; PinHeader_1x02_P2.54mm_Vertical
J3: B; PinHeader_1x01_P2.54mm_Vertical
J6: OUT; PinHeader_1x03_P2.54mm_Vertical
J7: C; PinHeader_1x01_P2.54mm_Vertical
J8: D; PinHeader_1x01_P2.54mm_Vertical
J9: E; PinHeader_1x01_P2.54mm_Vertical
J10: F; PinHeader_1x01_P2.54mm_Vertical
Q1, Q2, Q3, Q4, Q5, Q6, Q7, Q8, Q9: 2N2222; TO-92_Inline
R1, R2, R4, R6, R9, R10, R11, R12: 10K; R_Axial_DIN0309_L9.0mm_D3.2mm_P12.70mm_Horizontal
R3, R5, R7, R8: 1K; R_Axial_DIN0309_L9.0mm_D3.2mm_P12.70mm_Horizontal

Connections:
GND: C1.2, J2.2, J4.2, J5.2, Q1.1 (E), Q2.1 (E), Q3.1 (E), Q6.1 (E), Q7.1 (E), Q8.1 (E), Q9.1 (E), R7.2, R8.1
unnamed: D1.2 (A), Q5.1 (E)
unnamed: D1.1 (K), R8.2
unnamed: J1.1, R1.2
unnamed: J3.1, R2.2
unnamed: J6.1, J6.2, J6.3, Q4.1 (E), R7.1
unnamed: J7.1, R9.2
unnamed: J8.1, R10.2
unnamed: J9.1, R11.2
unnamed: J10.1, R12.2
unnamed: Q1.2 (B), R1.1
unnamed: Q1.3 (C), Q2.3 (C), Q6.3 (C), Q7.3 (C), Q8.3 (C), Q9.3 (C), R3.2, R4.2
unnamed: Q2.2 (B), R2.1
unnamed: Q3.2 (B), R4.1
unnamed: Q3.3 (C), Q4.2 (B), R5.2, R6.2
unnamed: Q5.2 (B), R6.1
unnamed: Q6.2 (B), R9.1
unnamed: Q7.2 (B), R10.1
unnamed: Q8.2 (B), R11.1
unnamed: Q9.2 (B), R12.1
VCC: C1.1, J2.1, J4.1, J5.1, Q4.3 (C), Q5.3 (C), R3.1, R5.1
